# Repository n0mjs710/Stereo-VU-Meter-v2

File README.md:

# Stereo-VU-Meter-v2
LED stereo VU meter display based on the MAX7221 LED driver IC

This display was originally developed to be used Arduino and Tennsy variants, but is very generic and useable on any 5VDC system with an SPI bus.

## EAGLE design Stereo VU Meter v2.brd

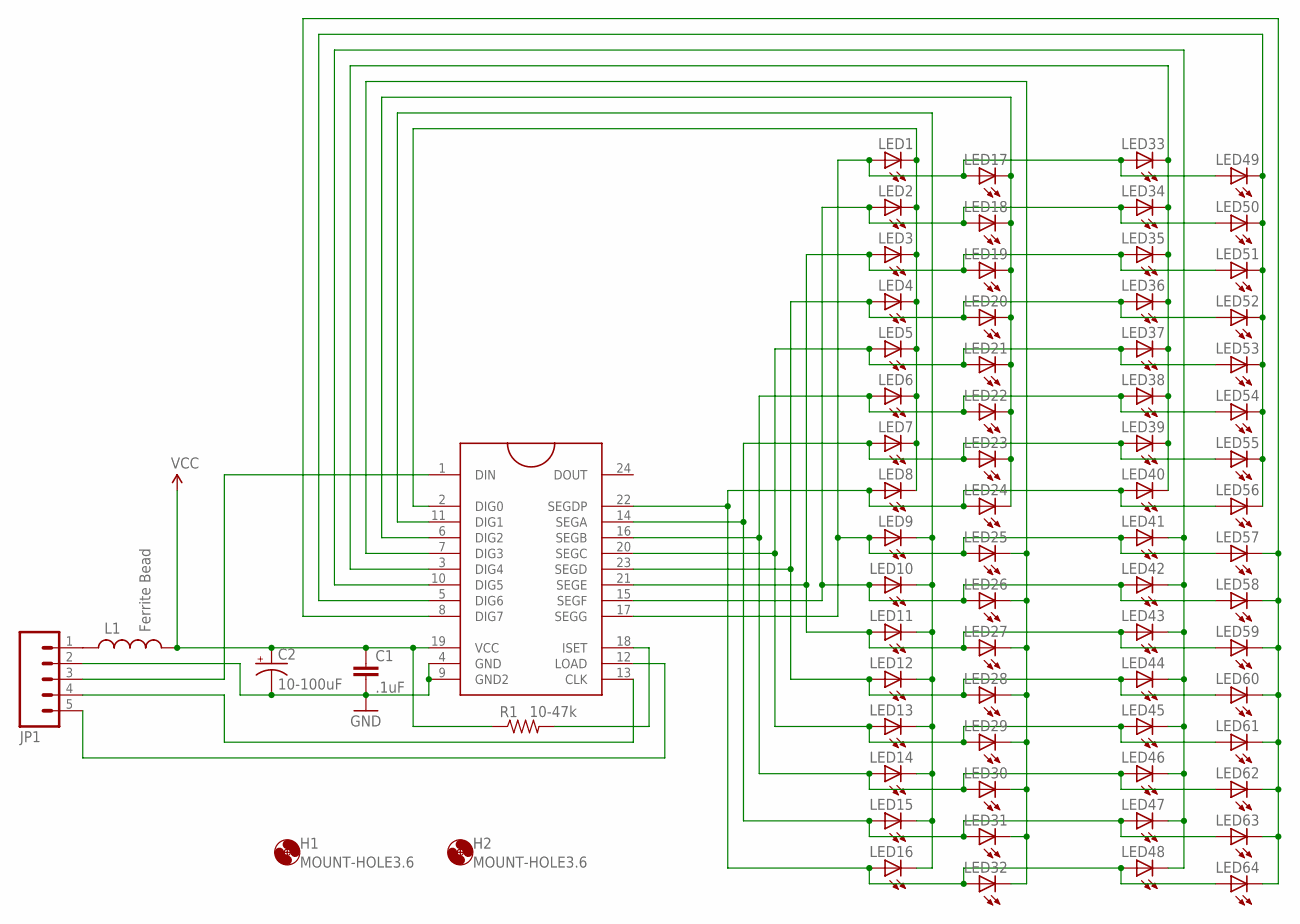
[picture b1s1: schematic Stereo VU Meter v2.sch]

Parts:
C1: .1uF; CAP-PTH-SMALLEZ
C2: 10-100uF; CPOL-RADIAL-10UF-25V
H1, H2: MOUNT-HOLE3.6; 3,6
JP1: M05PTH; 1X05
L1: Ferrite Bead; AXIAL-0.3
LED1, LED2, LED3, LED4, LED5, LED6, LED7, LED8, LED9, LED10, LED11, LED12, LED13, LED14, LED15, LED16, LED17, LED18, LED19, LED20, LED21, LED22, LED23, LED24, LED25, LED26, LED27, LED28, LED29, LED30, LED31, LED32, LED33, LED34, LED35, LED36, LED37, LED38, LED39, LED40, LED41, LED42, LED43, LED44, LED45, LED46, LED47, LED48, LED49, LED50, LED51, LED52, LED53, LED54, LED55, LED56, LED57, LED58, LED59, LED60, LED61, LED62, LED63, LED64: LED3MM
R1: 10-47k; AXIAL-0.3
U1: MAX7221DIP; DIL24

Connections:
GND: C1.2, C2.2 (-), JP1.2, U1.4 (GND), U1.9 (GND2)
unnamed: LED1.K (C), LED2.K (C), LED3.K (C), LED4.K (C), LED5.K (C), LED6.K (C), LED7.K (C), LED8.K (C), U1.2 (DIG0)
unnamed: LED9.K (C), LED10.K (C), LED11.K (C), LED12.K (C), LED13.K (C), LED14.K (C), LED15.K (C), LED16.K (C), U1.11 (DIG1)
unnamed: LED17.K (C), LED18.K (C), LED19.K (C), LED20.K (C), LED21.K (C), LED22.K (C), LED23.K (C), LED24.K (C), U1.6 (DIG2)
unnamed: LED33.K (C), LED34.K (C), LED35.K (C), LED36.K (C), LED37.K (C), LED38.K (C), LED39.K (C), LED40.K (C), U1.3 (DIG4)
unnamed: LED41.K (C), LED42.K (C), LED43.K (C), LED44.K (C), LED45.K (C), LED46.K (C), LED47.K (C), LED48.K (C), U1.10 (DIG5)
unnamed: LED49.K (C), LED50.K (C), LED51.K (C), LED52.K (C), LED53.K (C), LED54.K (C), LED55.K (C), LED56.K (C), U1.5 (DIG6)
unnamed: LED57.K (C), LED58.K (C), LED59.K (C), LED60.K (C), LED61.K (C), LED62.K (C), LED63.K (C), LED64.K (C), U1.8 (DIG7)
unnamed: LED1.A, LED9.A, LED17.A, LED25.A, LED33.A, LED41.A, LED49.A, LED57.A, U1.17 (SEGG)
unnamed: LED4.A, LED12.A, LED20.A, LED28.A, LED36.A, LED44.A, LED52.A, LED60.A, U1.23 (SEGD)
unnamed: LED25.K (C), LED26.K (C), LED27.K (C), LED28.K (C), LED29.K (C), LED30.K (C), LED31.K (C), LED32.K (C), U1.7 (DIG3)
unnamed: JP1.1, L1.P$1 (1)
unnamed: R1.P$2 (2), U1.18 (ISET)
unnamed: JP1.3, U1.1 (DIN)
unnamed: JP1.4, U1.13 (CLK)
unnamed: LED2.A, LED10.A, LED18.A, LED26.A, LED34.A, LED42.A, LED50.A, LED58.A, U1.15 (SEGF)
unnamed: LED3.A, LED11.A, LED19.A, LED27.A, LED35.A, LED43.A, LED51.A, LED59.A, U1.21 (SEGE)
unnamed: JP1.5, U1.12 (LOAD)
unnamed: LED5.A, LED13.A, LED21.A, LED29.A, LED37.A, LED45.A, LED53.A, LED61.A, U1.20 (SEGC)
unnamed: LED6.A, LED14.A, LED22.A, LED30.A, LED38.A, LED46.A, LED54.A, LED62.A, U1.16 (SEGB)
unnamed: LED7.A, LED15.A, LED23.A, LED31.A, LED39.A, LED47.A, LED55.A, LED63.A, U1.14 (SEGA)
unnamed: LED8.A, LED16.A, LED24.A, LED32.A, LED40.A, LED48.A, LED56.A, LED64.A, U1.22 (SEGDP)
VCC: C1.1, C2.1 (+), L1.P$2 (2), R1.P$1 (1), U1.19 (VCC)

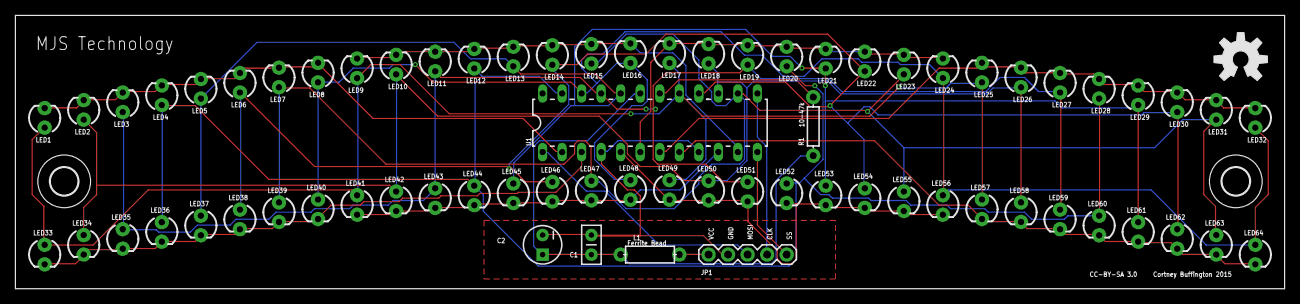
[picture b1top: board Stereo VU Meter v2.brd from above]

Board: 2 copper layers, 165.1 x 35.6 mm, 73 parts (0 on the bottom side), 23 nets.

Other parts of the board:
U$1: OSHW-LOGO-L

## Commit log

2015-04-11 Initial Upload

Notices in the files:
Stereo VU Meter v2.brd:
CC-BY-SA 3.0
parts and their libraries:
SparkFun-LED: Licensing: CC v3.0 Share-Alike You are welcome to use this library for commercial purposes.
